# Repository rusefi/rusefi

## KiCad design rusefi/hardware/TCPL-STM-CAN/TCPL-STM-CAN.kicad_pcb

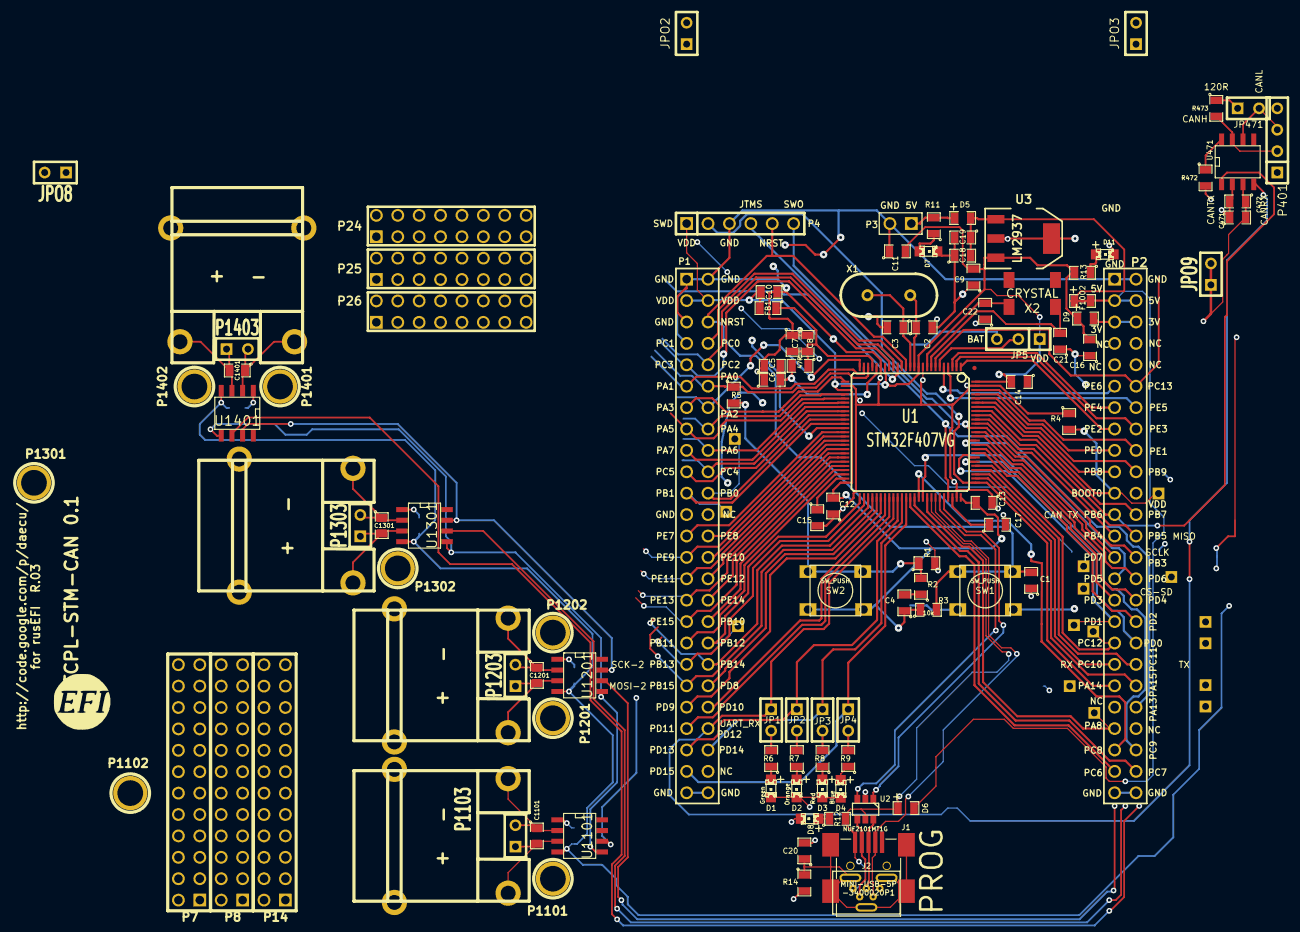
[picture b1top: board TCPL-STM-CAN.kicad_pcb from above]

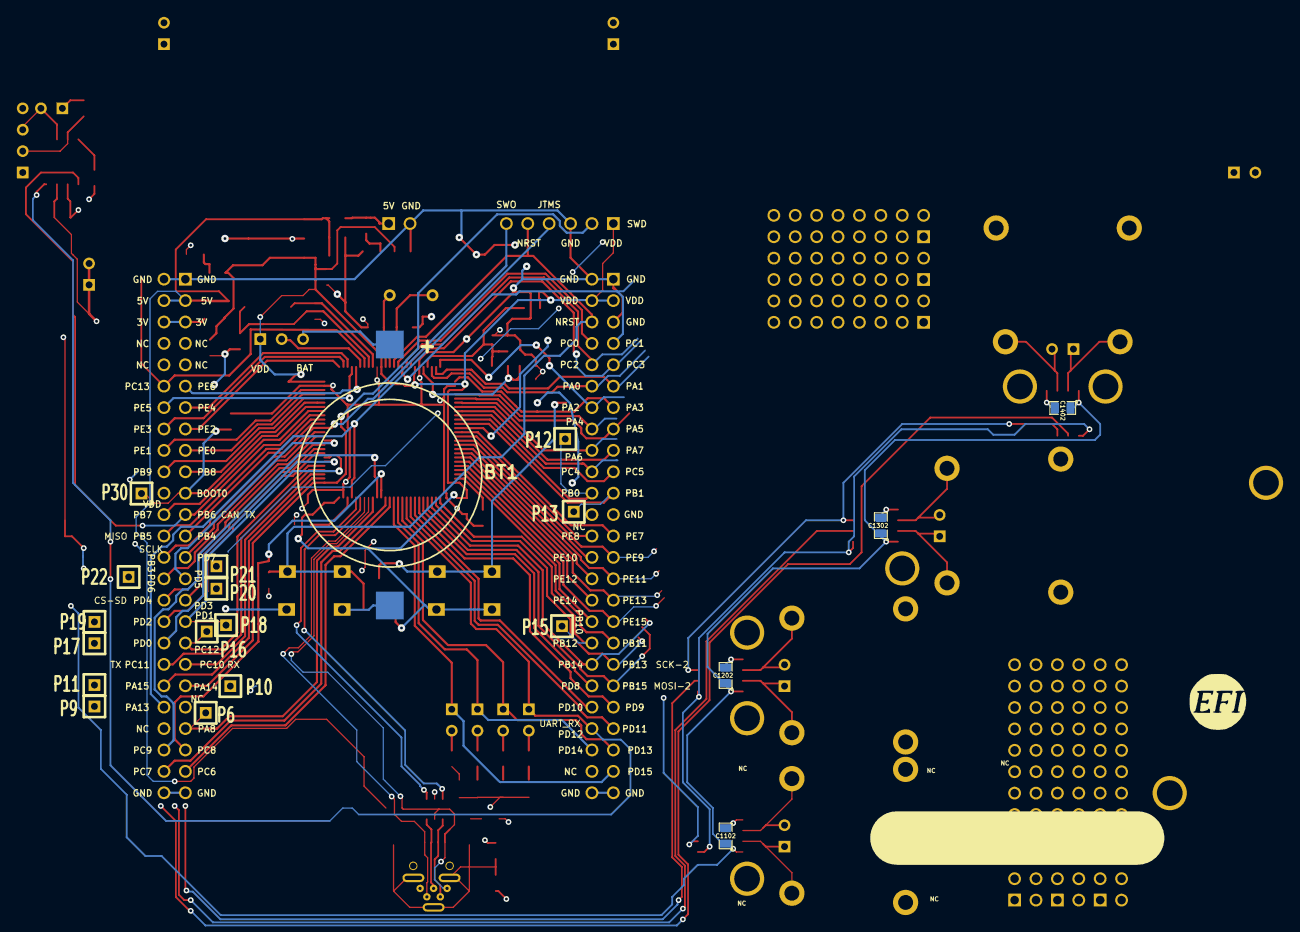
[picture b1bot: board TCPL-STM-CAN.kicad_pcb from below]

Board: 4 copper layers, 129 parts (21 on the bottom side), 124 nets.

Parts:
BT1: BATTERY_CR2032; BATT_CR2032_MPD
C1, C5, C8: 0.01uF; SM0805
C2, C3: 20pF; SM0805
C4, C15, C17: 2u2F; SM0805
C6, C7, C16: 1uF; SM0805
C9, C10, C11, C12, C13, C14, C18, C20, C471: 0.1uF; SM0805
C19, C472: 4.7uF; SM0805
C21, C22: 12.5pF; SM0805
C1101, C1201, C1301, C1401: 10nF; SM0805-SM0603
C1102, C1202, C1302, C1402: 100nF; SM0805-SM0603
D1, D7, D8, D11: LED-grn; LED-0805_A
D2: LED-org; LED-0805_A
D3: LED-red; LED-0805_A
D4: LED-blu; LED-0805_A
D5, D6, D9: DIODESCH; SM0805-diode
F1002: FUSE; SM0805-diode
FB1: FILTER; SM0805
G1: LOGO; LOGO_F
G2: LOGO
J1: MINI-USB-5P-3400020P1
J2: MINI-USB-5P-3400020P1V; MINI-USB_RCTP_V-T_B
JP1, JP2, JP3, JP4, JP471: JUMPER; JUMPER-2
JP5: JUMPER3; SIL-3
JPO2, JPO3, JPO8, JPO9: TEST-gnd; SIL-2
P1, P2: CONN_25X2; PIN_ARRAY_25x2_A
P3: CONN_2; PIN_ARRAY_2_A
P4: CONN_6; PIN_ARRAY-6X1
P6, P9, P10, P11, P12, P13, P15, P16, P17, P18, P19, P20, P21, P22, P30: CONN_1; SIL-1
P7, P8, P14: CONN_12X2; pin_array_12x2
P24, P25, P26: CONN_8X2; pin_array_8x2
P401: CONN_4; SIL-4
P1101, P1102, P1201, P1202, P1301, P1302, P1401, P1402: CONN_1; 1pin
P1103, P1203, P1303, P1403: CONN_2; SIL-2
P1104, P1204, P1304, P1404: CONN_2; tcpl_PCC-SMP
R1, R3, R4, R472: 10k; SM0805
R2: 100R; SM0805
R5: 330R; SM0805
R6, R7, R8, R9: 680R; SM0805
R10: 47R; SM0805
R11, R12, R13: 1k; SM0805
R14: 100k; SM0805
R473: 120; SM0805
SW1, SW2: SW_PUSH; TL-1105
U1: STM32F407VG; TQFP_100
U2: NUF2101MT1G; SOT-457
U3: LM2937; SOT223
U471: SN65HVD230; SO8E
U1101, U1201, U1301, U1401: MAX31855KASA; SO8E
X1: CRYSTAL; HC-49V
X2: CRYSTAL; MC-306

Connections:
/can_brd_1/3.3V: C471.2, C472.1, C1102.1, C1202.1, C1302.1, C1402.1, D9.2, JPO9.1, JPO9.2, P2.5, P2.6, U471.3, U1101.4, U1201.4, U1301.4, U1401.4
/can_brd_1/5V: C18.2, C19.1, D5.2, D6.2, F1002.1, F1002.2, JPO8.1, JPO8.2, P2.3, P2.4, P401.1, U3.1
/can_brd_1/CANH: P401.2, R473.2, U471.7
/can_brd_1/CANL: JP471.2, P401.3, U471.6
/can_brd_1/CAN_RX: JP1.1, P1.44, U1.59, U471.4
/can_brd_1/CAN_TX: P2.23, U1.92, U471.1
/stm32f407_board/BOOT0: P2.21, P30.1, R4.2, U1.94
/stm32f407_board/D+: J1.3, J2.3, U2.6
/stm32f407_board/D-: J1.2, J2.2, U2.4
/stm32f407_board/NRST: C1.2, P1.6, P4.5, R3.2, SW1.1, U1.14
/stm32f407_board/PA0: P1.12, R5.1, U1.23
/stm32f407_board/PA1: P1.11, U1.24
/stm32f407_board/PA2: P1.14, U1.25
/stm32f407_board/PA3: P1.13, U1.26
/stm32f407_board/PA4: P1.16, U1.29
/stm32f407_board/PA5: P1.15, U1.30
/stm32f407_board/PA6: P1.18, U1.31
/stm32f407_board/PA7: P1.17, U1.32
/stm32f407_board/PA9: D6.1, J1.1, J2.1, R12.2, U1.68, U2.5
/stm32f407_board/PA10: J1.4, J2.4, U1.69
/stm32f407_board/PA11: U1.70, U2.3
/stm32f407_board/PA12: U1.71, U2.1
/stm32f407_board/PA15: P2.40, P11.1, U1.77
/stm32f407_board/PB0: P1.22, P12.1, U1.35
/stm32f407_board/PB1: P1.21, P13.1, U1.36
/stm32f407_board/PB3: P2.28, P4.6, U1.89
/stm32f407_board/PB4: P2.25, U1.90
/stm32f407_board/PB5: P2.26, U1.91
/stm32f407_board/PB7: P2.24, U1.93
/stm32f407_board/PB8: P2.19, U1.95
/stm32f407_board/PB9: P2.20, U1.96
/stm32f407_board/PB10: P1.34, U1.47
/stm32f407_board/PB11: P1.35, U1.48
/stm32f407_board/PB13: P1.37, U1.52
/stm32f407_board/PB14: P1.38, U1.53
/stm32f407_board/PB15: P1.39, U1.54
/stm32f407_board/PC0: P1.8, U1.15
/stm32f407_board/PC1: P1.7, U1.16
/stm32f407_board/PC2: P1.10, U1.17
/stm32f407_board/PC3: P1.9, U1.18
/stm32f407_board/PC4: P1.20, U1.33
/stm32f407_board/PC5: P1.19, U1.34
/stm32f407_board/PC6: P2.47, U1.63
/stm32f407_board/PC7: P2.48, U1.64
/stm32f407_board/PC8: P2.45, U1.65
/stm32f407_board/PC9: P2.46, U1.66
/stm32f407_board/PC10: P2.37, U1.78
/stm32f407_board/PC11: P2.38, U1.79
/stm32f407_board/PC12: P2.35, P16.1, U1.80
/stm32f407_board/PC13: P2.12, U1.7
/stm32f407_board/PD0: P2.36, P17.1, U1.81
/stm32f407_board/PD1: P2.33, P18.1, U1.82
/stm32f407_board/PD2: P2.34, P19.1, U1.83
/stm32f407_board/PD3: P2.31, P20.1, U1.84
/stm32f407_board/PD4: P2.32, U1.85
/stm32f407_board/PD5: P2.29, P21.1, U1.86
/stm32f407_board/PD6: P2.30, P22.1, U1.87
/stm32f407_board/PD7: P2.27, U1.88
/stm32f407_board/PD8: P1.40, U1.55
/stm32f407_board/PD9: P1.41, U1.56
/stm32f407_board/PD10: P1.42, U1.57
/stm32f407_board/PD11: P1.43, U1.58
/stm32f407_board/PD13: JP2.1, P1.45, U1.60
/stm32f407_board/PD14: JP3.1, P1.46, U1.61
/stm32f407_board/PD15: JP4.1, P1.47, U1.62
/stm32f407_board/PE0: P2.17, U1.97
/stm32f407_board/PE1: P2.18, U1.98
/stm32f407_board/PE2: P2.15, U1.1
/stm32f407_board/PE3: P2.16, U1.2
/stm32f407_board/PE4: P2.13, U1.3
/stm32f407_board/PE5: P2.14, U1.4
/stm32f407_board/PE6: P2.11, U1.5
/stm32f407_board/PE7: P1.25, U1.38
/stm32f407_board/PE8: P1.26, U1.39
/stm32f407_board/PE9: P1.27, U1.40
/stm32f407_board/PE10: P1.28, U1.41
/stm32f407_board/PE11: P1.29, U1.42
/stm32f407_board/PE12: P1.30, U1.43
/stm32f407_board/PE13: P1.31, U1.44
/stm32f407_board/PE14: P1.32, U1.45
/stm32f407_board/PE15: P1.33, U1.46
/stm32f407_board/VDD: C4.1, C9.2, C10.2, C11.2, C12.2, C13.2, C14.2, C16.2, D9.1, FB1.2, JP5.1, P1.3, P1.4, P4.1, R3.1, R13.2, SW2.2, U1.11, U1.19, U1.28, U1.50, U1.75, U1.100, U3.3
/stm32f407_board/shield: C20.1, J1.6, J2.6, R14.1
/thermocouple1//CS: P1.36, P15.1, U1.51, U1101.6
/thermocouple1/MISO: U1101.7, U1201.7, U1301.7, U1401.7
/thermocouple1/SCK: U1101.5, U1201.5, U1301.5, U1401.5
/thermocouple1/TCPL+: C1101.2, P1103.1, P1104.2, U1101.3
/thermocouple1/TCPL-: C1101.1, P1103.2, P1104.1, U1101.2
/thermocouple2//CS: P2.39, P4.2, P10.1, U1.76, U1201.6
/thermocouple2/TCPL+: C1201.2, P1203.1, P1204.2, U1201.3
/thermocouple2/TCPL-: C1201.1, P1203.2, P1204.1, U1201.2
/thermocouple3//CS: P2.43, P6.1, U1.67, U1301.6
/thermocouple3/TCPL+: C1301.2, P1303.1, P1304.2, U1301.3
/thermocouple3/TCPL-: C1301.1, P1303.2, P1304.1, U1301.2
/thermocouple4//CS: P2.42, P4.4, P9.1, U1.72, U1401.6
/thermocouple4/TCPL+: C1401.2, P1403.1, P1404.2, U1401.3
/thermocouple4/TCPL-: C1401.1, P1403.2, P1404.1, U1401.2
GND: BT1.2, C1.1, C2.2, C3.2, C5.1, C6.1, C7.1, C8.1, C9.1, C10.1, C11.1, C12.1, C13.1, C14.1, C15.2, C16.1, C17.2, C18.1, C19.2, C20.2, C21.1, C22.1, C471.1, C472.2, C1102.2, C1202.2, C1302.2, C1402.2, D1.2, D2.2, D3.2, D4.2, D7.2, D8.2, D11.2, J1.5, J2.5, JPO2.1, JPO2.2, JPO3.1, JPO3.2, P1.1, P1.2, P1.5, P1.23, P1.49, P1.50, P2.1, P2.2, P2.49, P2.50, P3.2, P4.3, P401.4, R1.2, R4.1, R14.2, R472.2, SW1.2, U1.10, U1.20, U1.27, U1.37, U1.74, U1.99, U2.2, U3.2, U3.4, U471.2, U1101.1, U1201.1, U1301.1, U1401.1
unnamed: R472.1, U471.8
unnamed: JP471.1, R473.1
unnamed: C22.2, U1.9, X2.1
unnamed: C21.2, U1.8, X2.2
unnamed: C2.1, U1.12, X1.2
unnamed: D2.1, R7.1
unnamed: D3.1, R8.1
unnamed: D4.1, R9.1
unnamed: D7.1, R11.1
unnamed: D8.1, R12.1
unnamed: D11.1, R13.1
unnamed: D1.1, R6.1
unnamed: D5.1, P3.1, R11.2
unnamed: BT1.1, JP5.3
unnamed: JP5.2, U1.6
unnamed: JP4.2, R9.2
unnamed: JP3.2, R8.2
unnamed: JP2.2, R7.2
unnamed: JP1.2, R6.2
unnamed: R1.1, R2.2, R5.2, SW2.1
unnamed: C5.2, C6.2, R10.2, U1.21
unnamed: C3.1, U1.13, X1.1
unnamed: C17.1, U1.73
unnamed: C15.1, U1.49
unnamed: C4.2, R2.1
unnamed: C7.2, C8.2, FB1.1, R10.1, U1.22

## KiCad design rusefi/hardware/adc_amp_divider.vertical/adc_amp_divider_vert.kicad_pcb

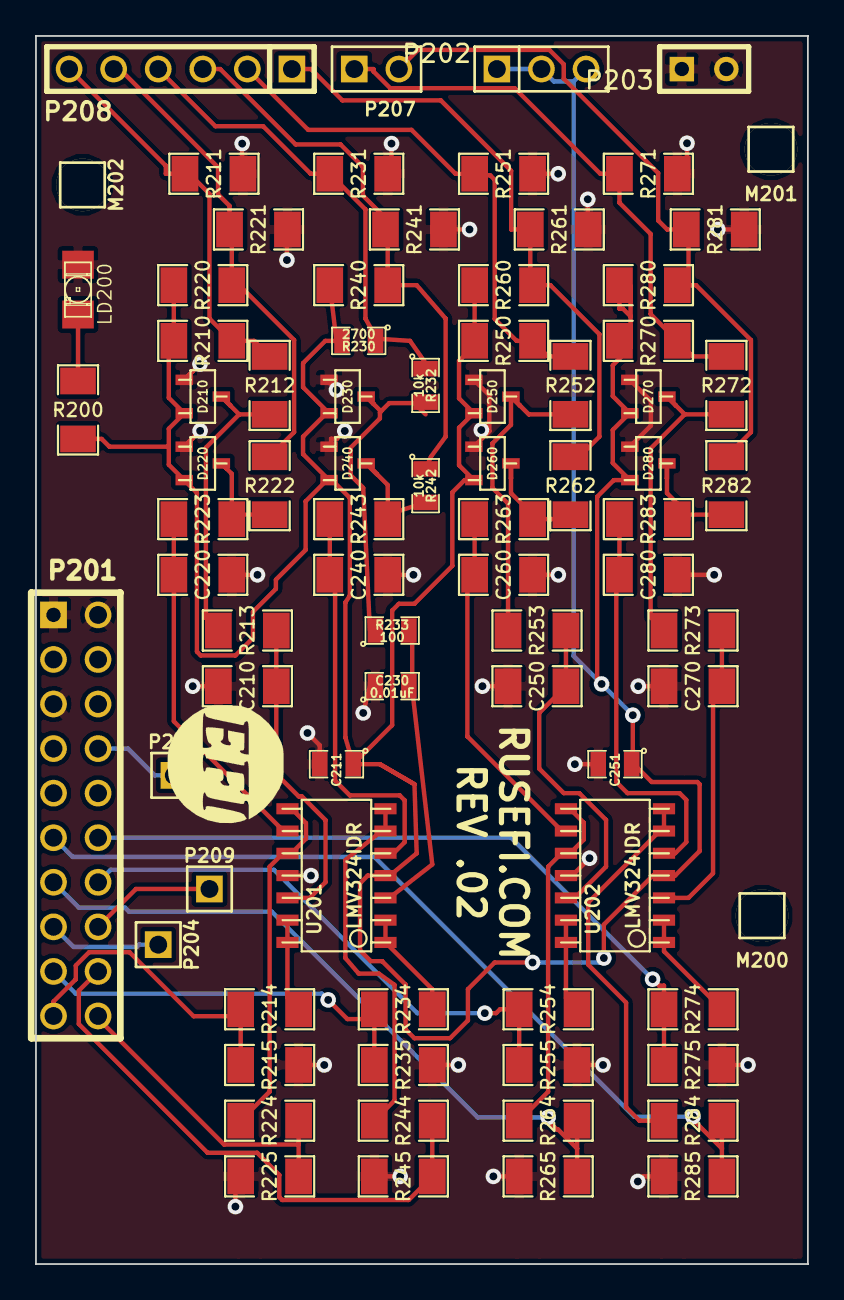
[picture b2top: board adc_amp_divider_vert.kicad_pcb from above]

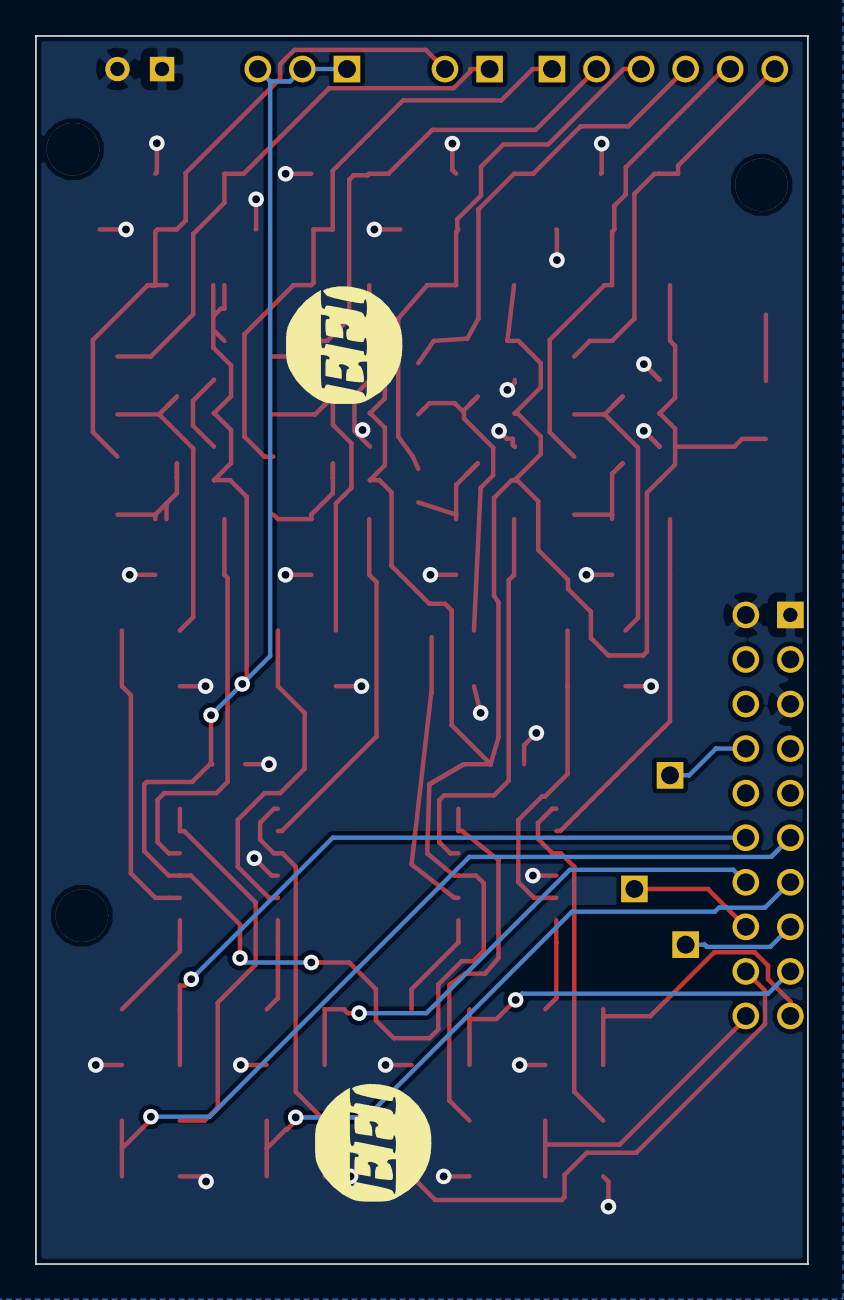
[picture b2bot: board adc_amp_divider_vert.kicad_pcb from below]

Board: 2 copper layers, 44.0 x 70.0 mm, 84 parts (2 on the bottom side), 46 nets.

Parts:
C210, C220, C240, C250, C260, C270, C280: 0.01uF; SM1206
C211, C251: 0.1uF; SM0805
C230: 0.01uF; SM0805
D210, D220, D230, D240, D250, D260, D270, D280: DOUBLE_SCHOTTKY; sot23
G200: LOGO
G201, G202: LOGO; LOGO_F
LD200: LED; LED-1206
M200, M201, M202: CONN_1; PIN_ARRAY_1
P201: CONN_10X2; PIN_ARRAY_10X2
P202: CONN_3; PIN_ARRAY_3X1
P203: CONN_2; SIL-2
P204, P205, P209: CONN_1; PIN_ARRAY_1
P207: CONN_2; PIN_ARRAY_2X1
P208: CONN_6; PIN_ARRAY-6X1
R200, R213, R223, R243, R253, R263, R273, R283: 100; SM1206
R210, R220, R240, R250, R260, R270, R280: 2700; SM1206
R211, R221, R231, R241, R251, R261, R271, R281: 500K; SM1206
R212, R222, R252, R262, R272, R282: 10k; SM1206
R214, R215, R224, R225, R234, R235, R244, R245, R254, R255, R264, R265, R274, R275, R284, R285: 1500; SM1206
R230: 2700; SM0805
R232, R242: 10k; SM0805
R233: 100; SM0805
U201, U202: LMV324IDR; so-14

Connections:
/5V: C211.1, C251.1, D210.3, D220.3, D230.3, D240.3, D250.3, D260.3, D270.3, D280.3, P202.1, P202.2, P202.3, R200.1, R210.2, R220.2, R230.2, R240.2, R250.2, R260.2, R270.2, R280.2, U201.4, U202.4
/INP1: P208.6, R210.1, R211.1, R212.1
/INP2: P208.5, R220.1, R221.1, R222.1
/INP3: P208.4, R230.1, R231.1, R232.1
/INP4: P208.3, R240.1, R241.1, R242.1
/INP5: P208.2, R250.1, R251.1, R252.1
/INP6: P208.1, R260.1, R261.1, R262.1
/INP7: P207.1, R270.1, R271.1, R272.1
/INP8: P207.2, R280.1, R281.1, R282.1
/OUT1: P201.19, R214.2, R215.1
/OUT2: P201.20, R224.2, R225.1
/OUT3: P201.17, R234.2, R235.1
/OUT4: P201.18, R244.2, R245.1
/OUT5: P201.14, R254.2, R255.1
/OUT6: P201.13, R264.2, R265.1
/OUT7: P201.12, R274.2, R275.1
/OUT8: P201.11, R284.2, R285.1
/PA4: P201.16, P209.1
/PA5: P201.15, P204.1
/PC0: P201.8, P205.1
GND: C210.1, C211.2, C220.1, C230.1, C240.1, C250.1, C251.2, C260.1, C270.1, C280.1, D210.1, D220.1, D230.1, D240.1, D250.1, D260.1, D270.1, D280.1, LD200.1, P201.1, P201.2, P201.5, P203.1, P203.2, R211.2, R215.2, R221.2, R225.2, R231.2, R235.2, R241.2, R245.2, R251.2, R255.2, R261.2, R265.2, R271.2, R275.2, R281.2, R285.2, U201.11, U202.11
unnamed: D240.2, R242.2, R243.1
unnamed: D220.2, R222.2, R223.1
unnamed: D250.2, R252.2, R253.1
unnamed: D260.2, R262.2, R263.1
unnamed: D210.2, R212.2, R213.1
unnamed: C280.2, R283.2, U202.5
unnamed: C270.2, R273.2, U202.3
unnamed: R284.1, U202.6, U202.7
unnamed: R274.1, U202.1, U202.2
unnamed: C240.2, R243.2, U201.5
unnamed: LD200.2, R200.2
unnamed: C260.2, R263.2, U202.9
unnamed: C250.2, R253.2, U202.12
unnamed: R264.1, U202.8, U202.10
unnamed: R254.1, U202.13, U202.14
unnamed: D270.2, R272.2, R273.1
unnamed: D280.2, R282.2, R283.1
unnamed: R244.1, U201.6, U201.7
unnamed: R234.1, U201.1, U201.2
unnamed: R224.1, U201.8, U201.10
unnamed: C220.2, R223.2, U201.9
unnamed: C210.2, R213.2, U201.12
unnamed: C230.2, R233.2, U201.3
unnamed: R214.1, U201.13, U201.14
unnamed: D230.2, R232.2, R233.1

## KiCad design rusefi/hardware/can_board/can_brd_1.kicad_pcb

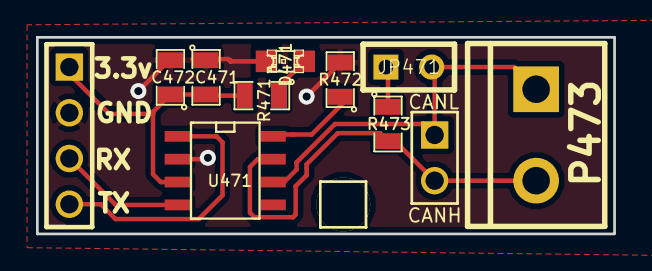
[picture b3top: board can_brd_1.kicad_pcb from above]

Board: 2 copper layers, 32.1 x 10.9 mm, 13 parts (1 on the bottom side), 9 nets.

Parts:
C471: .1uF; SM0805
C472: 4.7uF; SM0805
D471: RED; LED-0805_A
G471: LOGO; LOGO_F
JP471: JUMPER; JUMPER-2
M471: CONN_1; PIN_ARRAY_1
P471: CONN_4; PIN_ARRAY_4x1
P472: CONN_2; PIN_ARRAY_2_A
P473: CONN_2; bornier2
R471: 1k; SM0805
R472: 10k; SM0805
R473: 120; SM0805
U471: SN65HVD230; SO8E

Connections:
/3.3V: C471.2, C472.1, P471.1, R471.2, U471.3
/CANH: P472.2, P473.2, R473.2, U471.7
/CANL: JP471.2, P472.1, P473.1, U471.6
/CAN_RX: P471.3, U471.4
/CAN_TX: P471.4, U471.1
GND: C471.1, C472.2, D471.2, P471.2, R472.2, U471.2
unnamed: D471.1, R471.1
unnamed: JP471.1, R473.1
unnamed: R472.1, U471.8

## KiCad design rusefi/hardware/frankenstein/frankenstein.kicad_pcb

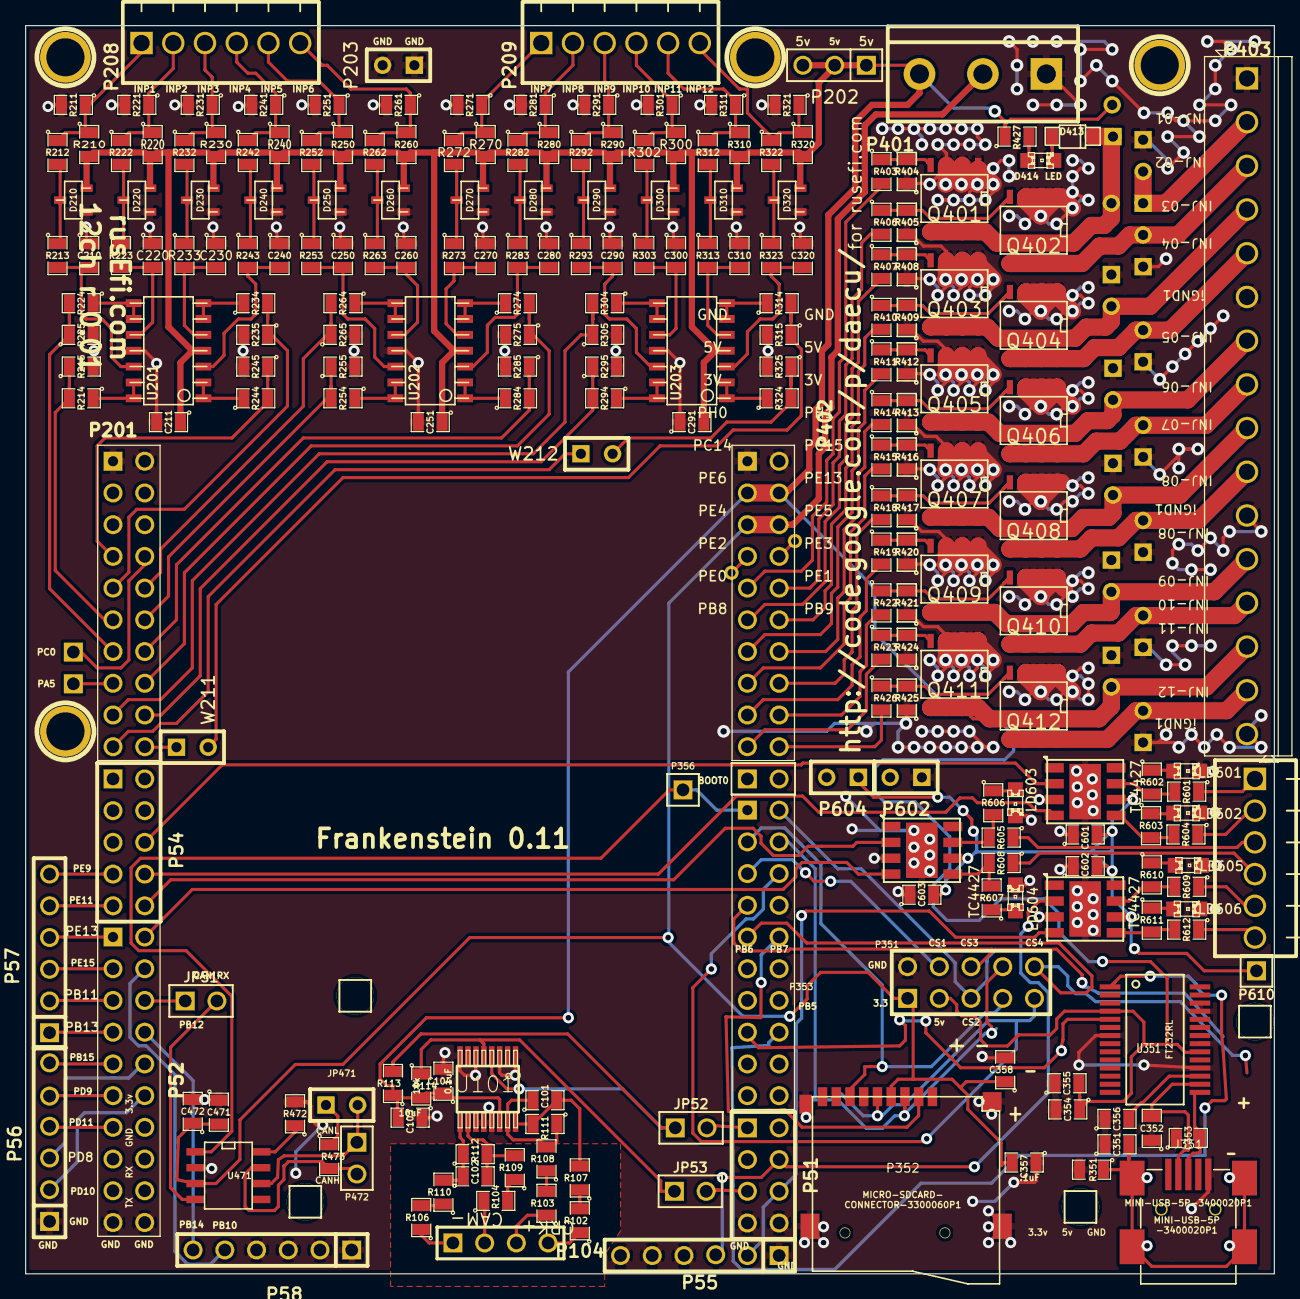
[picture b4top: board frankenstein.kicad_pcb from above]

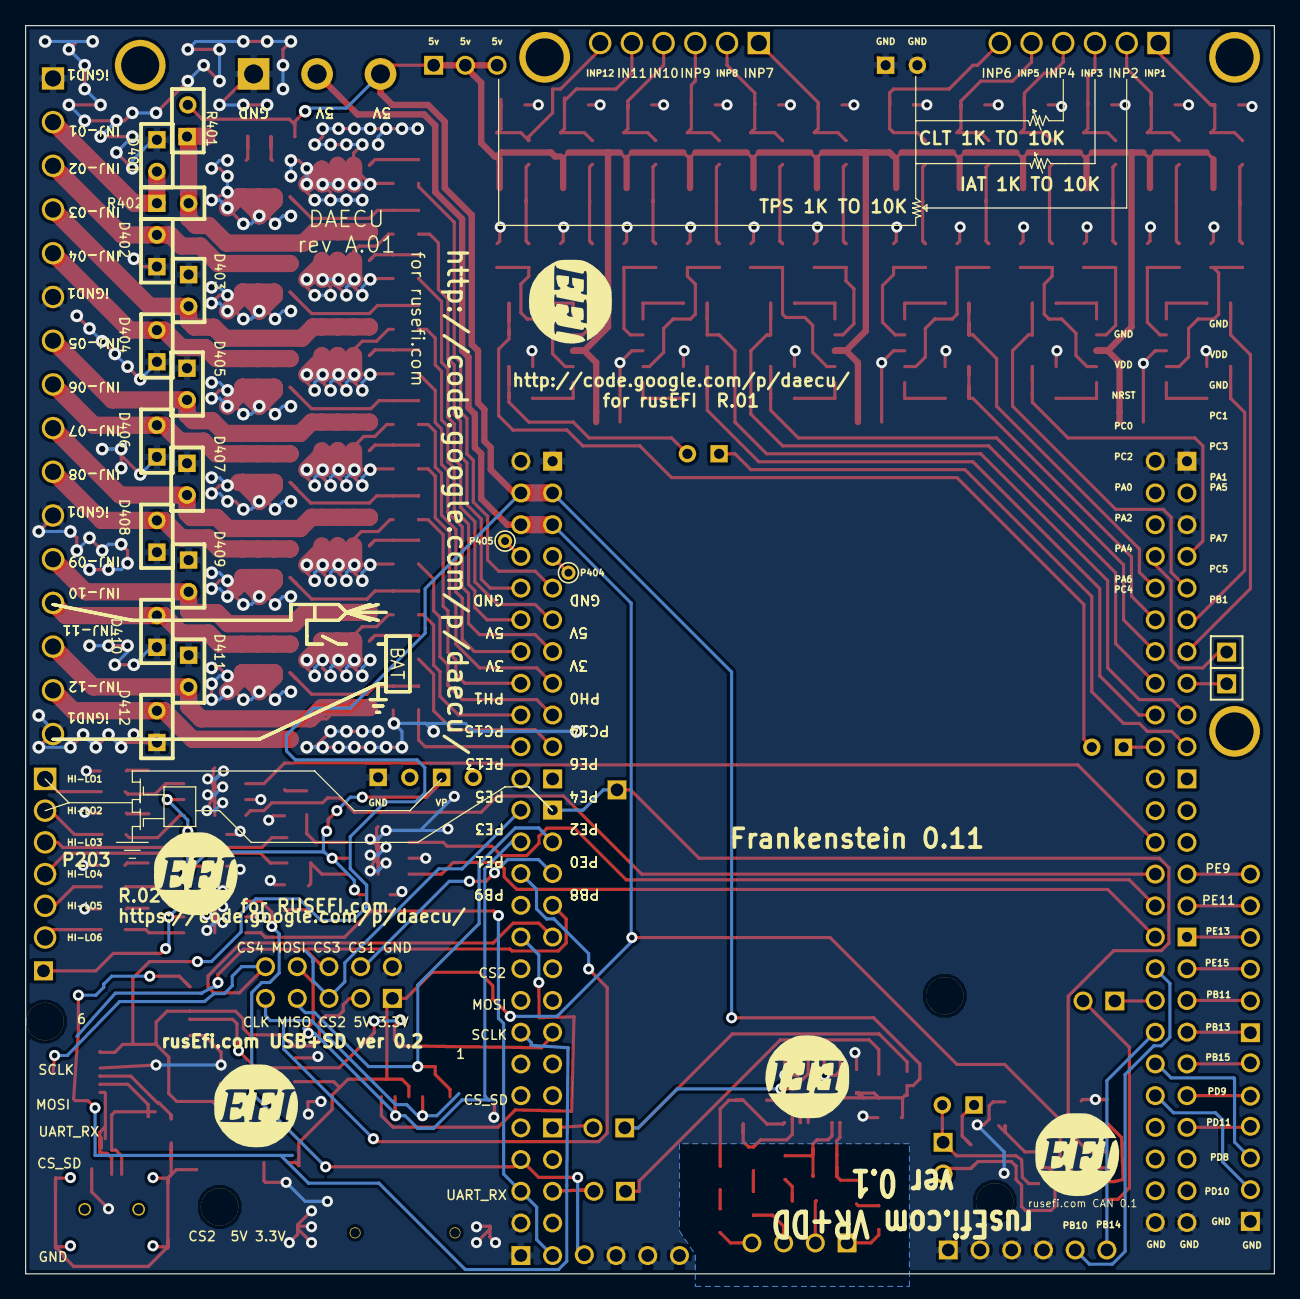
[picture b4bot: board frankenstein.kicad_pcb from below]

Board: 2 copper layers, 100.0 x 99.9 mm, 261 parts (23 on the bottom side), 183 nets.

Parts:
C101, C102: 1000pF; SM0805
C103: 10uF; SM0805
C104, C211, C251, C291, C601, C602, C603: 0.1uF; SM0805
C210, C220, C230, C240, C250, C260, C270, C280, C290, C300, C310, C320: 0.01uF; SM0805
C351: 4700pF; SM0805
C352, C353: 47pF; SM0805
C354, C358, C472: 4.7uF; SM0805
C355, C356, C357, C471: .1uF; SM0805
D210, D220, D230, D240, D250, D260, D270, D280, D290, D300, D310, D320: DOUBLE_SCHOTTKY; sot23
D401, D402, D403, D404, D405, D406, D407, D408, D409, D410, D411, D412: DIODE; SIL-2
D413: DIODE; SOD-123
D414: LED; LED-0805
G101, G201, G305, G471, G601: LOGO; LOGO_F
J351: MINI-USB-5P-3400020P1
JP51, JP52, JP53: JUMPER; PIN_ARRAY_2_A
JP471: JUMPER; SIL-2
LD601, LD602, LD603, LD604, LD605, LD606: LED; LED-0805
M200, M201, M202, M401: CONN_1; 1pin
M351, M352, M470, M471: CONN_1; PIN_ARRAY_1
P51: CONN_4X2; pin_array_4x2
P52, P201: CONN_10X2; PIN_ARRAY_10X2_M
P53: CONN_2; PIN_ARRAY_2X1
P54, P351: CONN_5X2; PIN_ARRAY_5x2
P55, P56, P57, P58: CONN_6; PIN_ARRAY-6X1
P104: CONN_4; PIN_ARRAY_4x1
P202: CONN_3; PIN_ARRAY_3X1
P203, P602, P604: CONN_2; SIL-2
P204, P205, P356, P610: CONN_1; PIN_ARRAY_1
P208, P209: CONN_6; 6_screw_term_.1in
P352: MICRO-SDCARD-CONNECTOR-3300060P1
P353: CONN_10X2; PIN_ARRAY_10X2
P401: CONN_3; bornier3
P402: CONN_10X2; pin_array_10x2
P403: CONN_16; SIL-16_3.5MM
P404, P405: CONN_1; PINTST
P472: CONN_2; PIN_ARRAY_2_A
P603: CONN_6; OSTVN06A150
Q401, Q402, Q403, Q404, Q405, Q406, Q407, Q408, Q409, Q410, Q411, Q412: OVP_DRIVER; SO8E_ST
R102, R103, R104, R106, R107, R108, R109, R110, R111, R112: 5k; SM0805
R113, R114, R212, R222, R232, R242, R252, R262, R272, R282, R292, R302, R312, R322, R472: 10k; SM0805
R210, R220, R230, R240, R250, R260, R270, R280, R290, R300, R310, R320, R602, R603, R606, R607, R610, R611: 2700; SM0805
R211, R221, R231, R241, R251, R261, R271, R281, R291, R301, R311, R321: 500K; SM0805
R213, R223, R233, R243, R253, R263, R273, R283, R293, R303, R313, R323, R601, R604, R605, R608, R609, R612: 100; SM0805
R214, R215, R224, R225, R234, R235, R244, R245, R254, R255, R264, R265, R274, R275, R284, R285, R294, R295, R304, R305, R314, R315, R324, R325: 1500; SM0805
R351: 1M; SM0805
R401: OPT; SIL-2
R402: 0R; SIL-2
R403, R406, R407, R410, R411, R414, R415, R418, R419, R422, R423, R426: 20R; SM0805
R404, R405, R408, R409, R412, R413, R416, R417, R420, R421, R424, R425, R427: 1K; SM0805
R473: 120; SM0805
U101: MAX9926/9927; maxim-10-QSOP16
U201, U202, U203: LMV324IDR; so-14
U351: FT232RL; ssop-28
U471: SN65HVD230; SO8E
U601, U602, U603: TC4427; SOIC8-DFN
W211, W212: TEST; SIL-2

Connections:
/3.3V: C357.2, C358.1, C471.2, C472.1, P351.1, P352.4, P401.2, P402.5, P402.6, U471.3
/5V: C103.2, C104.1, C211.1, C251.1, C291.2, C354.1, C355.2, D210.3, D220.3, D230.3, D240.3, D250.3, D260.3, D270.3, D280.3, D290.3, D300.3, D310.3, D320.3, P202.1, P202.2, P202.3, P351.3, P401.3, P402.3, P402.4, R113.1, R114.2, R210.2, R220.2, R230.2, R240.2, R250.2, R260.2, R270.2, R280.2, R290.2, R300.2, R310.2, R320.2, R401.2, R427.1, U101.14, U201.4, U202.4, U203.4, U351.4, U351.20
/CAM: JP53.1, R114.1, U101.5
/CAM+: P104.1, R106.1
/CAM-: P104.2, R104.1
/CANH: P472.2, R473.2, U471.7
/CANL: JP471.2, P472.1, U471.6
/CAN_RX: JP51.2, U471.4
/CAN_TX: P353.1, P356.1, U471.1
/CRANK: JP52.1, R113.2, U101.4
/CRK2+: P104.4, R102.1
/CRK2-: P104.3, R103.1
/CS1: P351.4, P353.5
/CS2: P351.5, P353.2
/CS3: P351.6, P353.7
/CS4: P351.10, P353.9
/CS_SD_MODULE: P352.2, P353.10
/HL1: P603.1, R601.1
/HL2: P603.2, R604.1
/HL3: P603.3, R605.1
/HL4: P603.4, R608.1
/HL5: P603.5, R609.1
/HL6: P603.6, R612.1
/H_IN1: P54.8, U601.4
/H_IN2: P54.10, U602.2
/H_IN3: P54.6, U601.2
/H_IN4: P52.2, U602.4
/H_IN5: P51.6, P55.2, U603.4
/H_IN6: P51.4, P55.3, U603.2
/INJ-01: D413.2, Q401.2, R401.1, R402.2
/INJ-01_2: D401.2, P403.2, R402.1
/INJ-01_5V: P402.9, R403.2
/INJ-02: D402.2, P403.3, Q402.2
/INJ-02_5V: P402.10, R406.2
/INJ-03: D403.2, P403.4, Q403.2
/INJ-03_5V: P402.11, R407.2
/INJ-04: D404.2, P403.5, Q404.2
/INJ-04_5V: P402.12, R410.2
/INJ-05: D405.2, P403.7, Q405.2
/INJ-05_5V: P402.13, R411.2
/INJ-06: D406.2, P403.8, Q406.2
/INJ-06_5V: P402.14, R414.2
/INJ-07: D407.2, P403.9, Q407.2
/INJ-07_5V: P402.15, R415.2
/INJ-08: D408.2, P403.10, Q408.2
/INJ-08_5V: P402.16, R418.2
/INJ-09: D409.2, P403.12, Q409.2
/INJ-09_5V: P402.17, R419.2
/INJ-10: D410.2, P403.13, Q410.2
/INJ-10_5V: P402.18, R422.2
/INJ-11: D411.2, P403.14, Q411.2
/INJ-11_5V: P402.19, R423.2
/INJ-12: D412.2, P403.15, Q412.2
/INJ-12_5V: P402.20, R426.2
/INP1: P208.1, R210.1, R211.1, R212.1
/INP2: P208.2, R220.1, R221.1, R222.1
/INP3: P208.3, R230.1, R231.1, R232.1
/INP4: P208.4, R240.1, R241.1, R242.1
/INP5: P208.5, R250.1, R251.1, R252.1
/INP6: P208.6, R260.1, R261.1, R262.1
/INP7: P209.1, R270.1, R271.1, R272.1
/INP8: P209.2, R280.1, R281.1, R282.1
/INP9: P209.3, R290.1, R291.1, R292.1
/INP10: P209.4, R300.1, R301.1, R302.1
/INP11: P209.5, R310.1, R311.1, R312.1
/INP12: P209.6, R320.1, R321.1, R322.1
/OUT1: P201.11, R214.2, R215.1
/OUT2: P201.13, R224.2, R225.1
/OUT3: P201.9, R234.2, R235.1
/OUT4: P201.7, R244.2, R245.1
/OUT5: P201.12, R254.2, R255.1
/OUT6: P201.10, R264.2, R265.1
/OUT7: P201.16, R274.2, R275.1
/OUT8: P201.14, R284.2, R285.1
/OUT9: P201.18, R294.2, R295.1
/OUT10: P201.17, R304.2, R305.1
/OUT11: P201.20, W211.1
/OUT12: P201.19, W212.1
/PA5: P201.15, P204.1
/PA8: JP52.2, P51.1
/PB10: P52.4, P58.5
/PB11: P52.5, P57.2
/PB12: JP51.1, P52.6
/PB13: P52.7, P57.1
/PB14: P52.8, P58.6
/PB15: P52.9, P56.6
/PC0: P201.8, P205.1
/PC6: JP53.2, P51.5
/PD8: P52.10, P56.3
/PD9: P52.11, P56.5
/PD10: P52.12, P56.2
/PD11: P52.13, P56.4
/PE9: P54.7, P57.6
/PE11: P54.9, P57.5
/PE13: P52.1, P57.4
/PE15: P52.3, P57.3
/PH0: P402.7, P404.1
/PH1: P402.8, P405.1
/SPI_MISO: P351.7, P352.7, P353.3
/SPI_MOSI: P351.8, P352.3, P353.4
/SPI_SCK: P351.9, P352.5, P353.6
/USART_RX: P353.15, U351.5
/USART_TX: P353.16, U351.1
/VP: C601.2, C602.2, C603.2, P604.1, P610.1, U601.6, U602.6, U603.6
F-000020: R102.2, R107.1
F-000021: R104.2, R109.1
F-000023: R106.2, R110.1
F-000024: R103.2, R108.1
F-000025: C101.1, R108.2, R111.1, U101.15
F-000026: C101.2, R107.2, R111.2, U101.16
F-000027: C102.1, R110.2, R112.1, U101.9
F-000028: C102.2, R109.2, R112.2, U101.10
F-000056: D280.2, R282.2, R283.1
F-000057: R214.1, U201.13, U201.14
F-000058: R224.1, U201.8, U201.9
F-000059: D270.2, R272.2, R273.1
F-000060: R244.1, U201.1, U201.2
F-000061: D300.2, R302.2, R303.1
F-000062: D290.2, R292.2, R293.1
F-000063: R304.1, U203.8, U203.9
F-000064: R294.1, U203.13, U203.14
F-000065: C290.2, R293.2, U203.12
F-000066: D250.2, R252.2, R253.1
F-000067: C300.2, R303.2, U203.10
F-000068: R314.1, U203.6, U203.7
F-000069: R324.1, U203.1, U203.2
F-000070: C310.2, R313.2, U203.5
F-000071: C320.2, R323.2, U203.3
F-000072: D320.2, R322.2, R323.1
F-000073: D260.2, R262.2, R263.1
F-000074: D310.2, R312.2, R313.1
F-000075: R324.2, R325.1, W212.2
F-000076: R314.2, R315.1, W211.2
F-000077: C250.2, R253.2, U202.12
F-000078: D210.2, R212.2, R213.1
F-000079: R254.1, U202.13, U202.14
F-000080: R274.1, U202.6, U202.7
F-000081: R264.1, U202.8, U202.9
F-000082: C240.2, R243.2, U201.3
F-000083: C230.2, R233.2, U201.5
F-000084: C270.2, R273.2, U202.5
F-000085: C280.2, R283.2, U202.3
F-000086: C220.2, R223.2, U201.10
F-000087: D220.2, R222.2, R223.1
F-000088: C210.2, R213.2, U201.12
F-000089: C260.2, R263.2, U202.10
F-000090: R284.1, U202.1, U202.2
F-000091: D240.2, R242.2, R243.1
F-000093: D230.2, R232.2, R233.1
F-000094: R234.1, U201.6, U201.7
F-0000108: C353.2, J351.3, U351.15
F-0000110: C351.2, J351.6, R351.1
F-0000112: C356.2, U351.17
F-0000115: C352.2, J351.4, U351.16
F-0000143: Q408.1, R417.2, R418.1
F-0000144: Q404.1, R409.2, R410.1
F-0000145: Q406.1, R413.2, R414.1
F-0000146: Q402.1, R405.2, R406.1
F-0000147: D414.1, R427.2
F-0000148: Q410.1, R421.2, R422.1
F-0000149: D413.1, D414.2
F-0000150: Q412.1, R425.2, R426.1
F-0000151: Q401.1, R403.1, R404.2
F-0000152: Q405.1, R411.1, R412.2
F-0000153: Q403.1, R407.1, R408.2
F-0000154: Q409.1, R419.1, R420.2
F-0000155: Q407.1, R415.1, R416.2
F-0000156: Q411.1, R423.1, R424.2
F-0000161: JP471.1, R473.1
F-0000162: R472.1, U471.8
GND: C103.1, C104.2, C210.1, C211.2, C220.1, C230.1, C240.1, C250.1, C251.2, C260.1, C270.1, C280.1, C290.1, C291.1, C300.1, C310.1, C320.1, C351.1, C352.1, C353.1, C354.2, C355.1, C356.1, C357.1, C358.2, C471.1, C472.2, C601.1, C602.1, C603.1, D210.1, D220.1, D230.1, D240.1, D250.1, D260.1, D270.1, D280.1, D290.1, D300.1, D310.1, D320.1, D401.1, D402.1, D403.1, D404.1, D405.1, D406.1, D407.1, D408.1, D409.1, D410.1, D411.1, D412.1, J351.1, LD601.2, LD602.2, LD603.2, LD604.2, LD605.2, LD606.2, P51.7, P51.8, P52.19, P52.20, P55.1, P55.4, P55.5, P55.6, P56.1, P58.1, P58.2, P58.3, P58.4, P201.1, P201.2, P201.5, P203.1, P203.2, P351.2, P352.6, P352.G1, P352.G2, P352.G3, P352.G4, P401.1, P402.1, P402.2, P403.1, P403.6, P403.11, P403.16, P602.1, Q401.3, Q402.3, Q403.3, Q404.3, Q405.3, Q406.3, Q407.3, Q408.3, Q409.3, Q410.3, Q411.3, Q412.3, R211.2, R215.2, R221.2, R225.2, R231.2, R235.2, R241.2, R245.2, R251.2, R255.2, R261.2, R265.2, R271.2, R275.2, R281.2, R285.2, R291.2, R295.2, R301.2, R305.2, R311.2, R315.2, R321.2, R325.2, R351.2, R404.1, R405.1, R408.1, R409.1, R412.1, R413.1, R416.1, R417.1, R420.1, R421.1, R424.1, R425.1, R472.2, U101.1, U101.3, U101.6, U101.8, U101.11, U101.12, U101.13, U201.11, U202.11, U203.11, U351.7, U351.18, U351.21, U351.25, U351.26, U471.2, U601.3, U601.9, U602.3, U602.9, U603.3, U603.9
unnamed: LD604.1, R607.1
unnamed: LD602.1, R603.1
unnamed: LD605.1, R610.1
unnamed: LD603.1, R606.1
unnamed: LD601.1, R602.1
unnamed: R609.2, R610.2, U603.7
unnamed: R603.2, R604.2, U601.5
unnamed: R601.2, R602.2, U601.7
unnamed: R607.2, R608.2, U602.5
unnamed: R605.2, R606.2, U602.7
unnamed: LD606.1, R611.1
unnamed: R611.2, R612.2, U603.5

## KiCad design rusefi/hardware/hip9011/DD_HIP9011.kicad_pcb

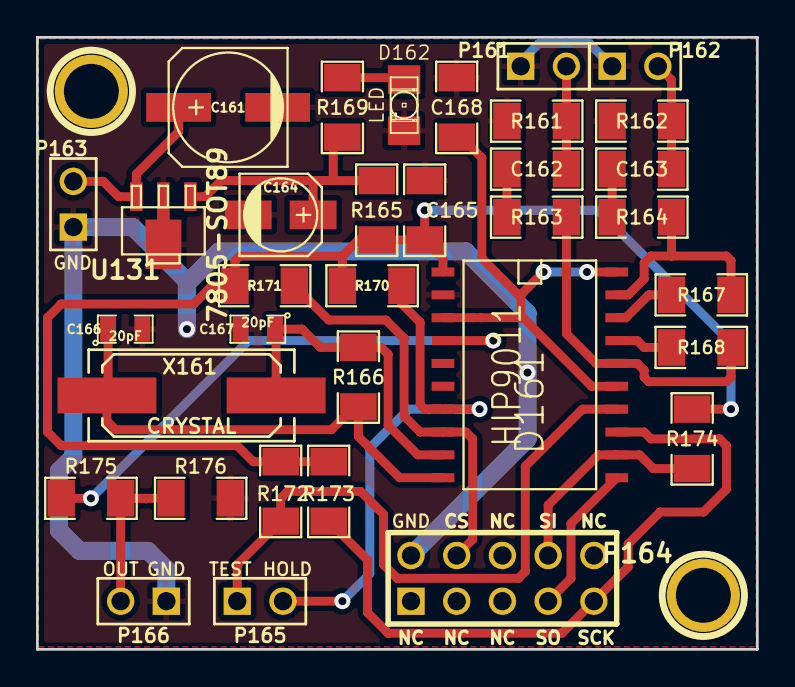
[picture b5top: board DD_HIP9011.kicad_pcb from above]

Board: 2 copper layers, 40.0 x 34.0 mm, 35 parts (1 on the bottom side), 24 nets.

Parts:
C161: 100u; c_elec_6.3x5.3
C162, C163: 47n; SM1206
C164: 10u; c_elec_4x5.3
C165: 100n; SM1206
C166, C167: 20pF; SM0805
C168: 22n; SM1206
D161: HIP9011; SO20L
D162: LED; LED-1206
G161: LOGO; LOGO_F
P161: KNOCK 1; PIN_ARRAY_2X1
P162: KNOCK 2; PIN_ARRAY_2X1
P163: 12V; PIN_ARRAY_2X1
P164: CONN_5X2; PIN_ARRAY_5x2
P165, P166: CONN_2; PIN_ARRAY_2X1
R161, R162, R166: 1M; SM1206
R163, R164, R175, R176: 10k; SM1206
R165: 10R; SM1206
R167, R168: 68k; SM1206
R169: 470R; SM1206
R170, R171, R172, R173, R174: 1K; SM1206
U131: 7805-SOT89; sot89
X161: CRYSTAL; Q_49U3HMS

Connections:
/5V: C165.1, D161.1, R165.2, R170.1, R171.1, R172.1, R173.1, R174.1
/+12V: C161.1, P163.2, U131.3
/CS: D161.8, P164.4, R171.2
/GND: C161.2, C164.2, C165.2, C166.2, C167.2, C168.2, D161.2, D162.2, P161.1, P162.1, P163.1, P164.2, P166.1, R161.2, R162.2, R176.2, U131.2
/INT/HLD: D161.7, P165.2, R170.2
/INTOUT: D161.4, R175.1
/KNOCK1: C162.1, P161.2, R161.1
/KNOCK2: C163.1, P162.2, R162.1
/OUT: P166.2, R175.2, R176.1
/SCK: D161.13, P164.9, R173.2
/SI: D161.12, P164.8, R174.2
/SO: D161.11, P164.7
/TEST: D161.14, P165.1, R172.2
unnamed: D162.1, R169.1
unnamed: C164.1, R165.1, R169.2, U131.1
unnamed: C167.1, D161.9, R166.2, X161.1
unnamed: C166.1, D161.10, R166.1, X161.2
unnamed: C163.2, R164.1
unnamed: C168.1, D161.3, D161.15, D161.20
unnamed: D161.16, R163.2, R168.2
unnamed: D161.17, R168.1
unnamed: D161.18, R167.1
unnamed: D161.19, R164.2, R167.2
unnamed: C162.2, R163.1

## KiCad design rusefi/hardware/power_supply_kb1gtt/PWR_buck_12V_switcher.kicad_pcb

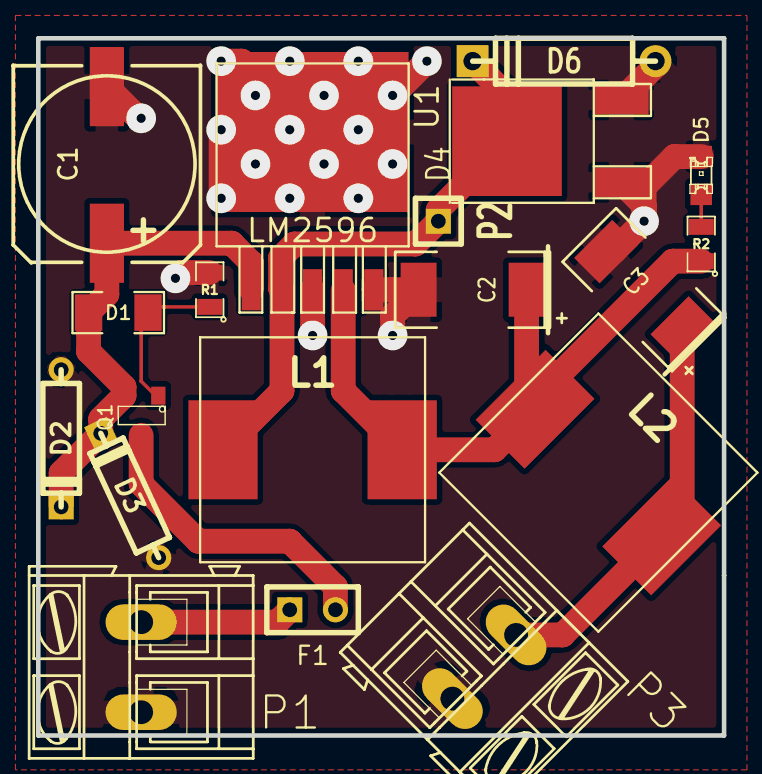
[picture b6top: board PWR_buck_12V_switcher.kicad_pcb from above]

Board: 2 copper layers, 38.1 x 38.7 mm, 19 parts (0 on the bottom side), 9 nets.

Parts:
C1: 470uF 25V; SMDSVP10
C2, C3: 220uF 16V; SM2512
D1: ZENERSMALL; SM1206
D2, D3: TVS; D3
D4: SCHDPAK; DPAK2
D5: GREEN; LED-0805
D6: DIODESCH; D4
F1: 3.5A; SIL-2
L1, L2: 38uH; SM100uH
P1, P3: CONN_2; AK300-2
P2: CONN_1; SIL-1
Q1: MOS_PRO; SOT23
R1, R2: 1k; SM0805
U1: LM2596; DPAK5

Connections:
/5V-REG: C3.1, L2.2, P3.1
/FB: C2.1, L1.2, L2.1, R2.1, U1.4
/OUT: D4.2, D6.2, L1.1, P2.1, U1.2
/VBAT: C1.1, D1.2, D2.2, D3.2, Q1.2, U1.1
/Vf: F1.2, Q1.3
/Vin: F1.1, P1.2
GND: C1.2, C2.2, C3.2, D2.1, D3.1, D4.1, D4.3, D5.2, D6.1, P1.1, P3.2, R1.2, U1.3, U1.5
unnamed: D1.1, Q1.1, R1.1
unnamed: D5.1, R2.2
